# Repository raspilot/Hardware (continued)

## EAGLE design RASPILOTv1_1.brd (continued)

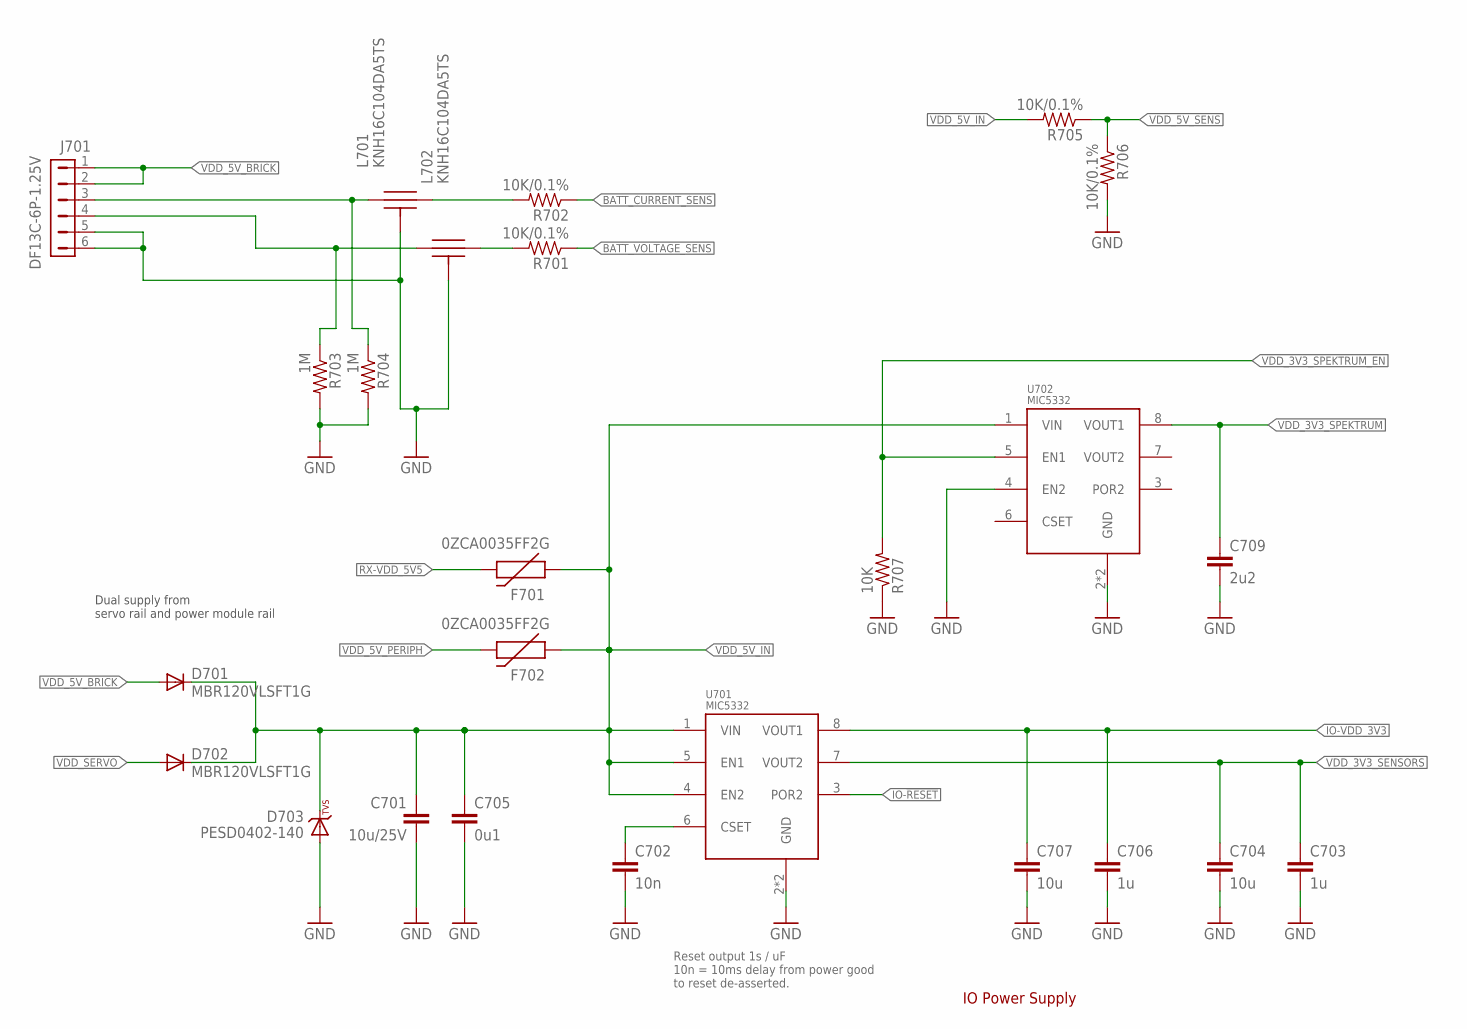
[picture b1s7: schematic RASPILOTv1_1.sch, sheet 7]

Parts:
C701: 10u/25V; 0805-CAP; PARTNO CL21A106KAYNNNE
C702: 10n; 0402-CAP; PARTNO CC0402KRX7R7BB103
C703, C706: 1u; 0603-CAP; PARTNO CC0603ZRY5V7BB105
C704, C707: 10u; 0603-CAP; PARTNO C1608X5R1A106K080AC
C705: 0u1; 0402-CAP; PARTNO CC0402ZRY5V7BB104
C709: 2u2; 0402-CAP; PARTNO C1005X6S1C225K050BC
D701, D702: MBR120VLSFT1G; SOD-123-DIO
D703: PESD0402-140; 0402-TVS; PARTNO PESD0402-140
F701, F702: 0ZCA0035FF2G; PTC-1206; PARTNO 0ZCA0035FF2G
J701: DF13C-6P-1.25V; PARTNO DF13C-6P-1.25V(20)
L701, L702: KNH16C104DA5TS; KYOCERA-KNH16-DA; PARTNO KNH16C104DA5TS
R701, R702, R705, R706: 10K/0.1%; 0402-RES; PARTNO ERA-2AEB103X
R703, R704: 1M; 0402-RES; PARTNO RC0402FR-071ML
R707: 10K; 0402-RES; PARTNO RC0402FR-0710KL
U701, U702: MIC5332; MLF-8-EPAD; PARTNO MIC5332-SSYMT

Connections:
BATT_CURRENT_SENS: R702.P$1 (1); also elsewhere on the board
BATT_CURRENT_SENS_PROT1: J701.3, L701.P$1, R704.P$1 (1)
BATT_VOLTAGE_SENS: R701.P$1 (1); also elsewhere on the board
BATT_VOLTAGE_SENS_PROT1: J701.4, L702.P$1, R703.P$1 (1)
GND: C701.P$2 (2), C702.P$2 (2), C703.P$2 (2), C704.P$2 (2), C705.P$2 (2), C706.P$2 (2), C707.P$2 (2), C709.P$2 (2), D703.A, J701.5, J701.6, L701.P$3, L701.P$4, L701.P$5, L702.P$3, L702.P$4, L702.P$5, R703.P$2 (2), R704.P$2 (2), R706.P$2 (2), R707.P$1 (1), U701.2 (GND), U701.GND, U702.2 (GND), U702.4 (EN2), U702.GND; also elsewhere on the board
IO-!RESET: U701.3 (POR2); also elsewhere on the board
IO-VDD_3V3: C706.P$1 (1), C707.P$1 (1), U701.8 (VOUT1); also elsewhere on the board
unnamed: L702.P$2, R701.P$2 (2)
unnamed: L701.P$2, R702.P$2 (2)
unnamed: C702.P$1 (1), U701.6 (CSET)
RX-VDD_5V5: F701.2; also elsewhere on the board
VDD_3V3_SENSORS: C703.P$1 (1), C704.P$1 (1), U701.7 (VOUT2); also elsewhere on the board
VDD_3V3_SPEKTRUM: C709.P$1 (1), U702.8 (VOUT1); also elsewhere on the board
VDD_3V3_SPEKTRUM_EN: R707.P$2 (2), U702.5 (EN1); also elsewhere on the board
VDD_5V_BRICK: D701.A, J701.1, J701.2; also elsewhere on the board
VDD_5V_IN: C701.P$1 (1), C705.P$1 (1), D701.C, D702.C, D703.C, F701.1, F702.1, R705.P$2 (2), U701.1 (VIN), U701.4 (EN2), U701.5 (EN1), U702.1 (VIN); also elsewhere on the board
VDD_5V_PERIPH: F702.2; also elsewhere on the board
VDD_5V_SENS: R705.P$1 (1), R706.P$1 (1); also elsewhere on the board
VDD_SERVO: D702.A; also elsewhere on the board

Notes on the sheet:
Dual supply from servo rail and power module rail
IO Power Supply
Reset output 1s / uF 10n = 10ms delay from power good to reset de-asserted.

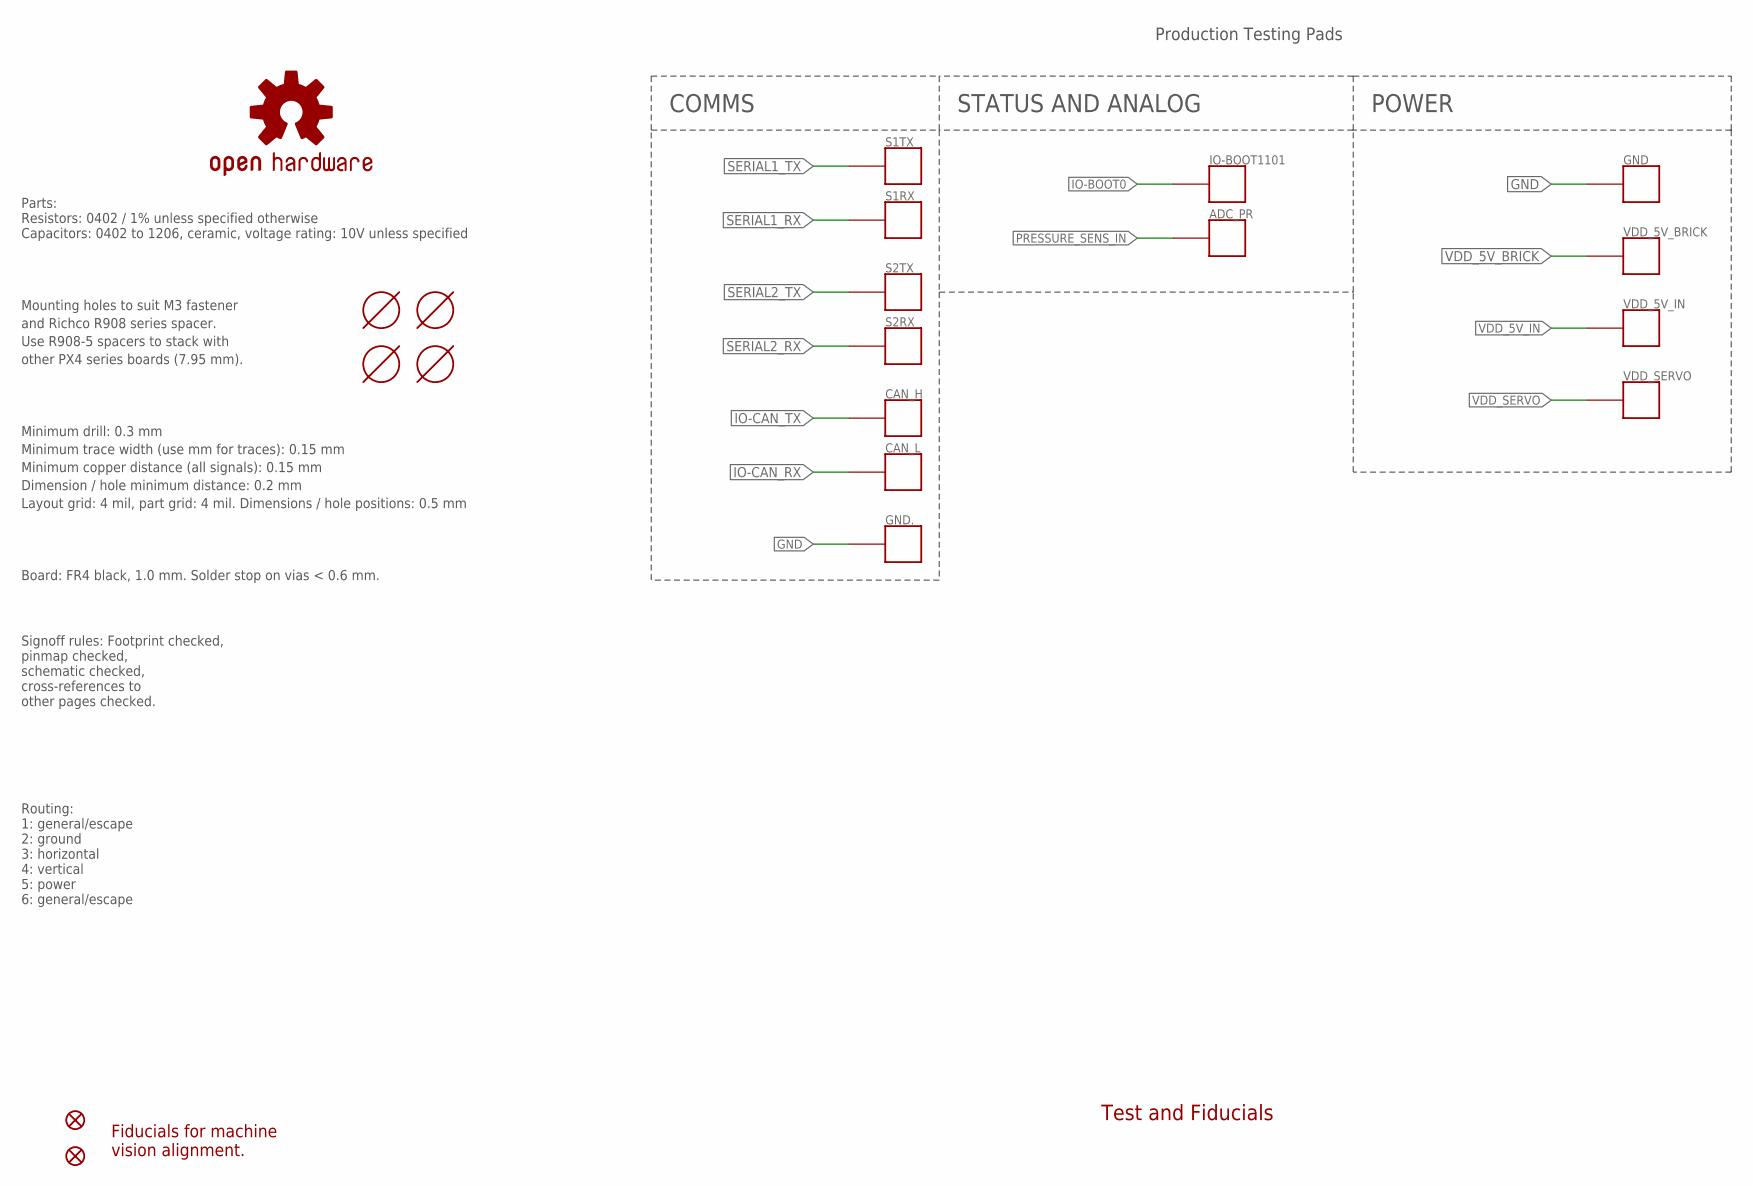
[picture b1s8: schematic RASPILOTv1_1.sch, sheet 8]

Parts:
ADC_PR: PAD.04; PAD.04X.04; PARTNO *
CAN_H: PAD.04; PAD.04X.04; PARTNO *
CAN_L: PAD.04; PAD.04X.04; PARTNO *
GND, GND.: PAD.04; PAD.04X.04; PARTNO *
IO-BOOT1101: PAD.04; PAD.04X.04; PARTNO *
JP1, JP2: FIDUCIAL1.5X3; FIDUCIAL-1.5X3; PARTNO *
M3_MOUNT1101, M3_MOUNT1102, M3_MOUNT1103, M3_MOUNT1104: MOUNT-HOLE3.1MM; MOUNT-HOLE3.1; PARTNO *
OSHW_LOGO: OSHW-LOGOS; OSHW-LOGO-S; PARTNO *
S1RX, S1TX, S2RX, S2TX: PAD.04; PAD.04X.04; PARTNO *
VDD_5V_BRICK, VDD_5V_IN: PAD.04; PAD.04X.04; PARTNO *
VDD_SERVO: PAD.04; PAD.04X.04; PARTNO *

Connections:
GND: GND.P$1, GND..P$1; also elsewhere on the board
IO-BOOT0: IO-BOOT1101.P$1; also elsewhere on the board
IO-CAN_RX: CAN_L.P$1; also elsewhere on the board
IO-CAN_TX: CAN_H.P$1; also elsewhere on the board
PRESSURE_SENS_IN: ADC_PR.P$1; also elsewhere on the board
SERIAL1_RX: S1RX.P$1; also elsewhere on the board
SERIAL1_TX: S1TX.P$1; also elsewhere on the board
SERIAL2_RX: S2RX.P$1; also elsewhere on the board
SERIAL2_TX: S2TX.P$1; also elsewhere on the board
VDD_5V_BRICK: VDD_5V_BRICK.P$1; also elsewhere on the board
VDD_5V_IN: VDD_5V_IN.P$1; also elsewhere on the board
VDD_SERVO: VDD_SERVO.P$1; also elsewhere on the board

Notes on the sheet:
Mounting holes to suit M3 fastener
and Richco R908 series spacer.
Use R908-5 spacers to stack with
other PX4 series boards (7.95 mm).
Production Testing Pads
Test and Fiducials
Minimum drill: 0.3 mm
Minimum trace width (use mm for traces): 0.15 mm
Minimum copper distance (all signals): 0.15 mm
Dimension / hole minimum distance: 0.2 mm
Layout grid: 4 mil, part grid: 4 mil. Dimensions / hole positions: 0.5 mm
Board: FR4 black, 1.0 mm. Solder stop on vias < 0.6 mm.
Signoff rules: Footprint checked, pinmap checked, schematic checked, cross-references to other pages checked.
Routing: 1: general/escape 2: ground 3: horizontal 4: vertical 5: power 6: general/escape
Fiducials for machine vision alignment.
Parts: Resistors: 0402 / 1% unless specified otherwise Capacitors: 0402 to 1206, ceramic, voltage rating: 10V unless specified
COMMS
POWER
STATUS AND ANALOG

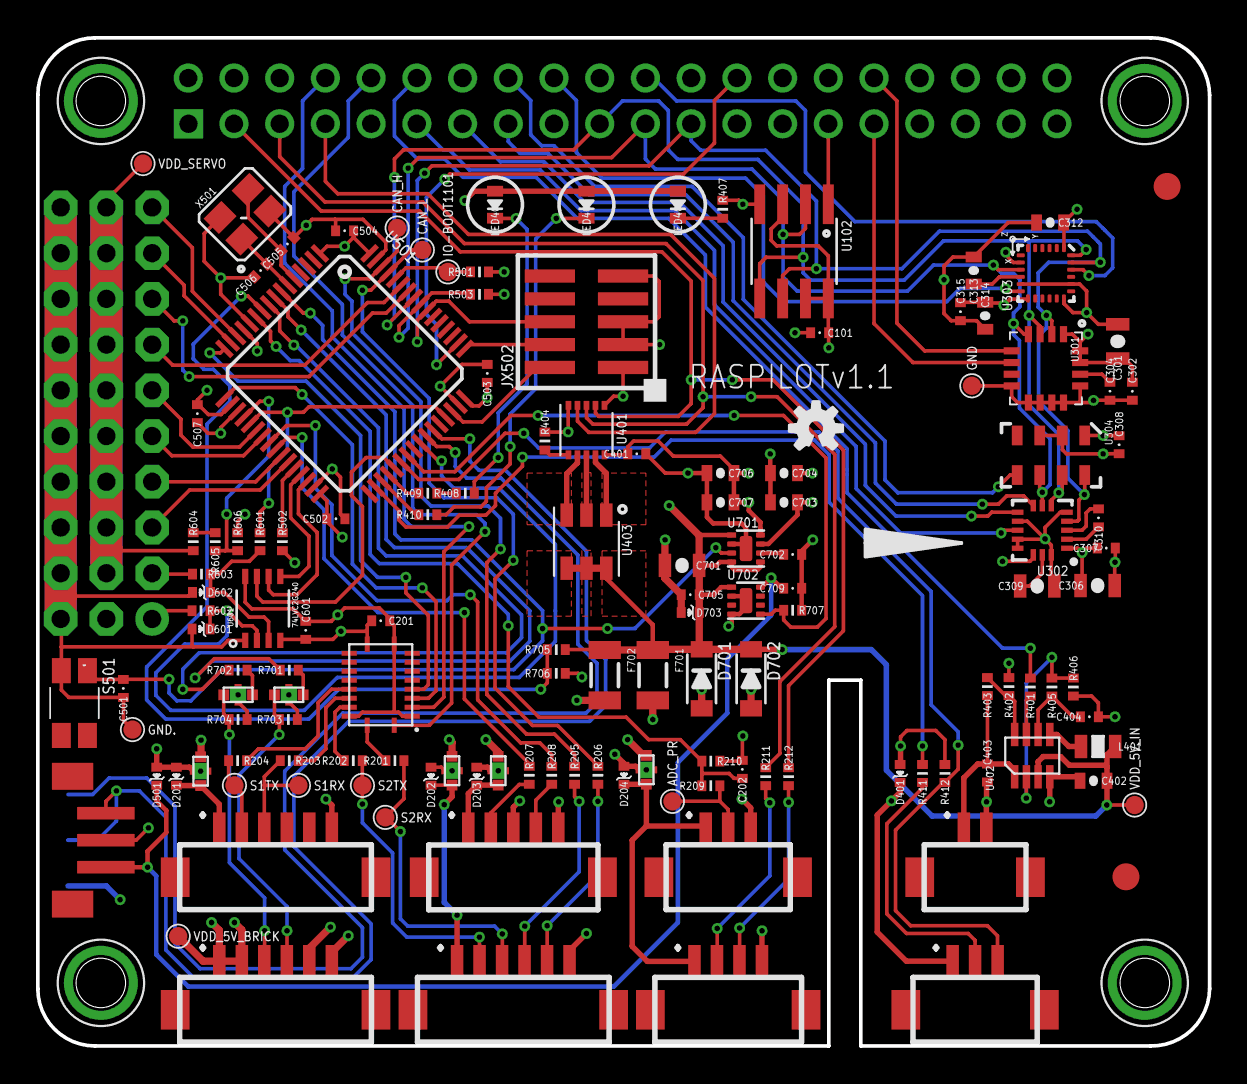
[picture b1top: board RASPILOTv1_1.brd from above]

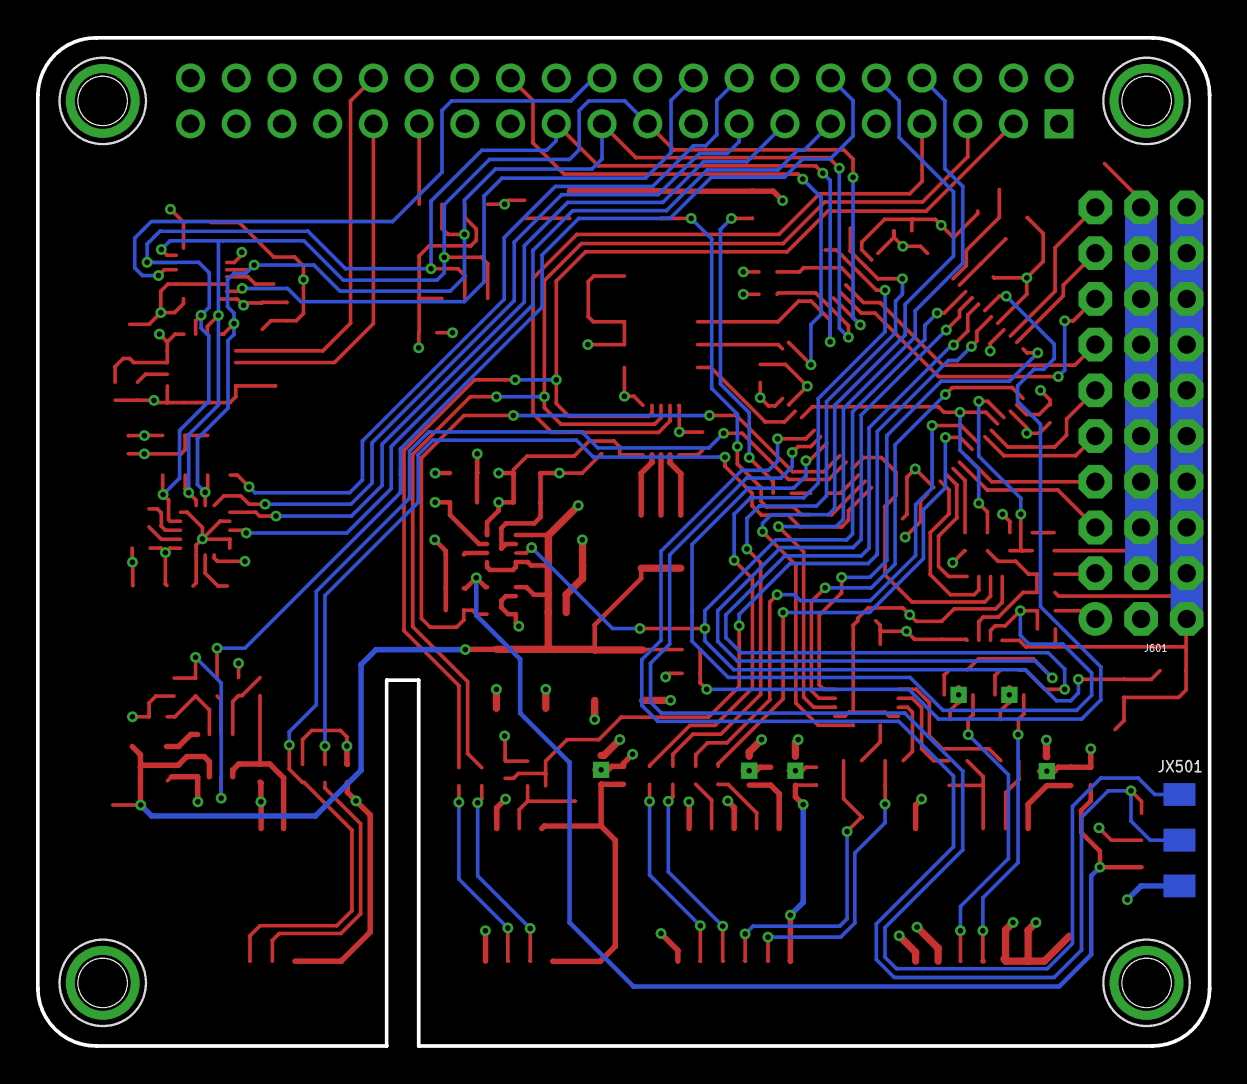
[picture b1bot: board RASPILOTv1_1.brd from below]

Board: 4 copper layers, 65.1 x 56.0 mm, 146 parts (2 on the bottom side), 114 nets.

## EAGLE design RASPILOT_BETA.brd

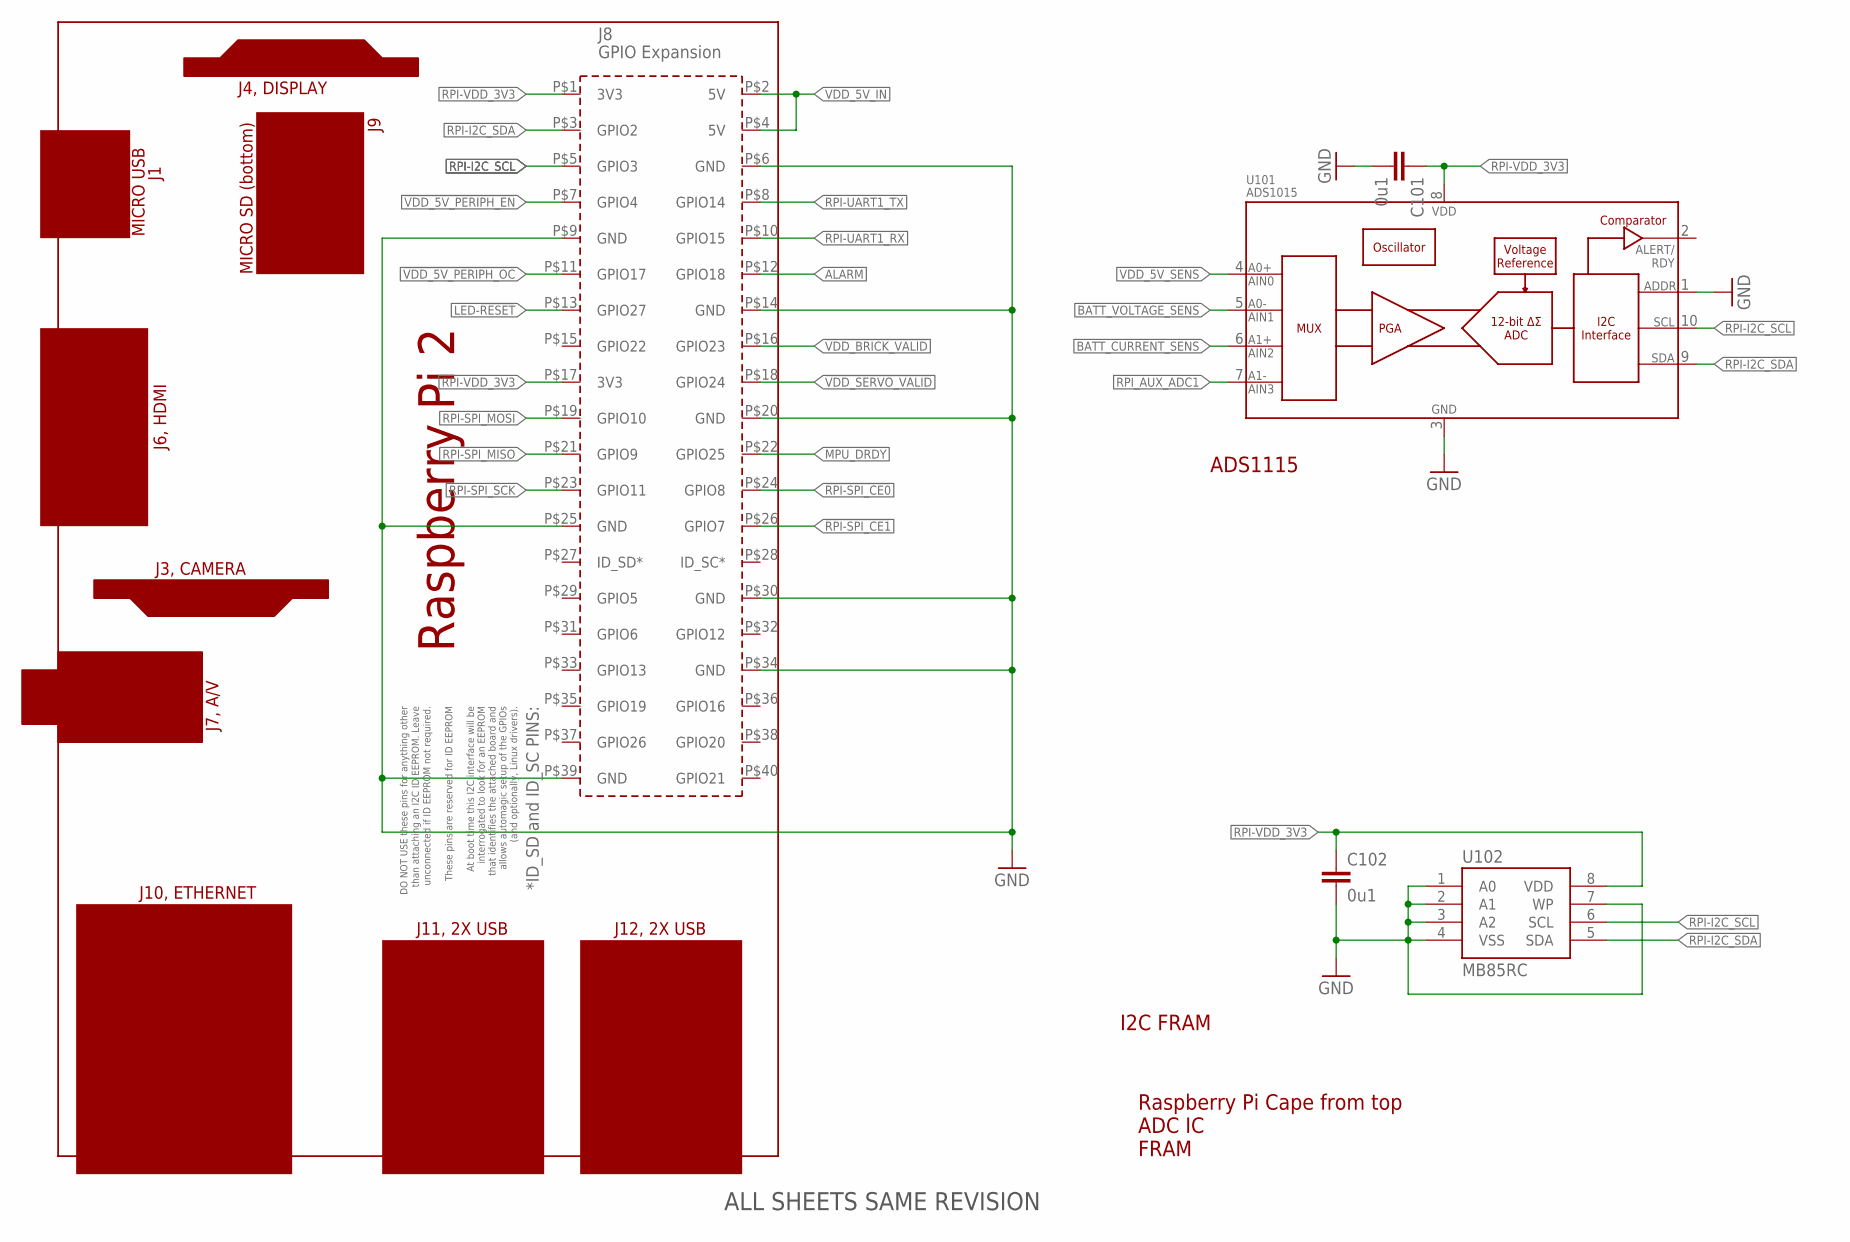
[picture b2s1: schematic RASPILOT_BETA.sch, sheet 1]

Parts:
C101, C102: 0u1; 0402-CAP; PARTNO CC0402ZRY5V7BB104
J101: RPI2
U101: ADS1015; MSOP10
U102: MB85RC; SOP8

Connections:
!RPI-SPI_CE0: J101.P$24 (GPIO8); also elsewhere on the board
!RPI-SPI_CE1: J101.P$26 (GPIO7); also elsewhere on the board
!VDD_5V_PERIPH_EN: J101.P$7 (GPIO4); also elsewhere on the board
!VDD_5V_PERIPH_OC: J101.P$11 (GPIO17); also elsewhere on the board
!VDD_BRICK_VALID: J101.P$16 (GPIO23); also elsewhere on the board
!VDD_SERVO_VALID: J101.P$18 (GPIO24); also elsewhere on the board
ALARM: J101.P$12 (GPIO18); also elsewhere on the board
BATT_CURRENT_SENS: U101.6 (AIN2); also elsewhere on the board
BATT_VOLTAGE_SENS: U101.5 (AIN1); also elsewhere on the board
GND: C101.P$2 (2), C102.P$2 (2), J101.P$6 (GND), J101.P$9 (GND), J101.P$14 (GND), J101.P$20 (GND), J101.P$25 (GND), J101.P$30 (GND), J101.P$34 (GND), J101.P$39 (GND), U101.1 (ADDR), U101.3 (VSS), U102.1 (A0), U102.2 (A1), U102.3 (A2), U102.4 (VSS), U102.7 (WP); also elsewhere on the board
LED-!RESET: J101.P$13 (GPIO27); also elsewhere on the board
MPU_DRDY: J101.P$22 (GPIO25); also elsewhere on the board
RPI-I2C_SCL: J101.P$5 (GPIO3), U101.10 (SCL), U102.6 (SCL); also elsewhere on the board
RPI-I2C_SDA: J101.P$3 (GPIO2), U101.9 (SDA), U102.5 (SDA); also elsewhere on the board
RPI-SPI_MISO: J101.P$21 (GPIO9); also elsewhere on the board
RPI-SPI_MOSI: J101.P$19 (GPIO10); also elsewhere on the board
RPI-SPI_SCK: J101.P$23 (GPIO11); also elsewhere on the board
RPI-UART1_RX: J101.P$10 (GPIO15); also elsewhere on the board
RPI-UART1_TX: J101.P$8 (GPIO14); also elsewhere on the board
RPI-VDD_3V3: C101.P$1 (1), C102.P$1 (1), J101.P$1 (3V3), J101.P$17 (3V3), U101.8 (VDD), U102.8 (VDD); also elsewhere on the board
RPI_AUX_ADC1: U101.7 (AIN3); also elsewhere on the board
VDD_5V_IN: J101.P$2 (5V), J101.P$4 (5V); also elsewhere on the board
VDD_5V_SENS: U101.4 (AIN0); also elsewhere on the board

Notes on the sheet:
Raspberry Pi Cape from top ADC IC FRAM
ALL SHEETS SAME REVISION
ADS1115
I2C FRAM

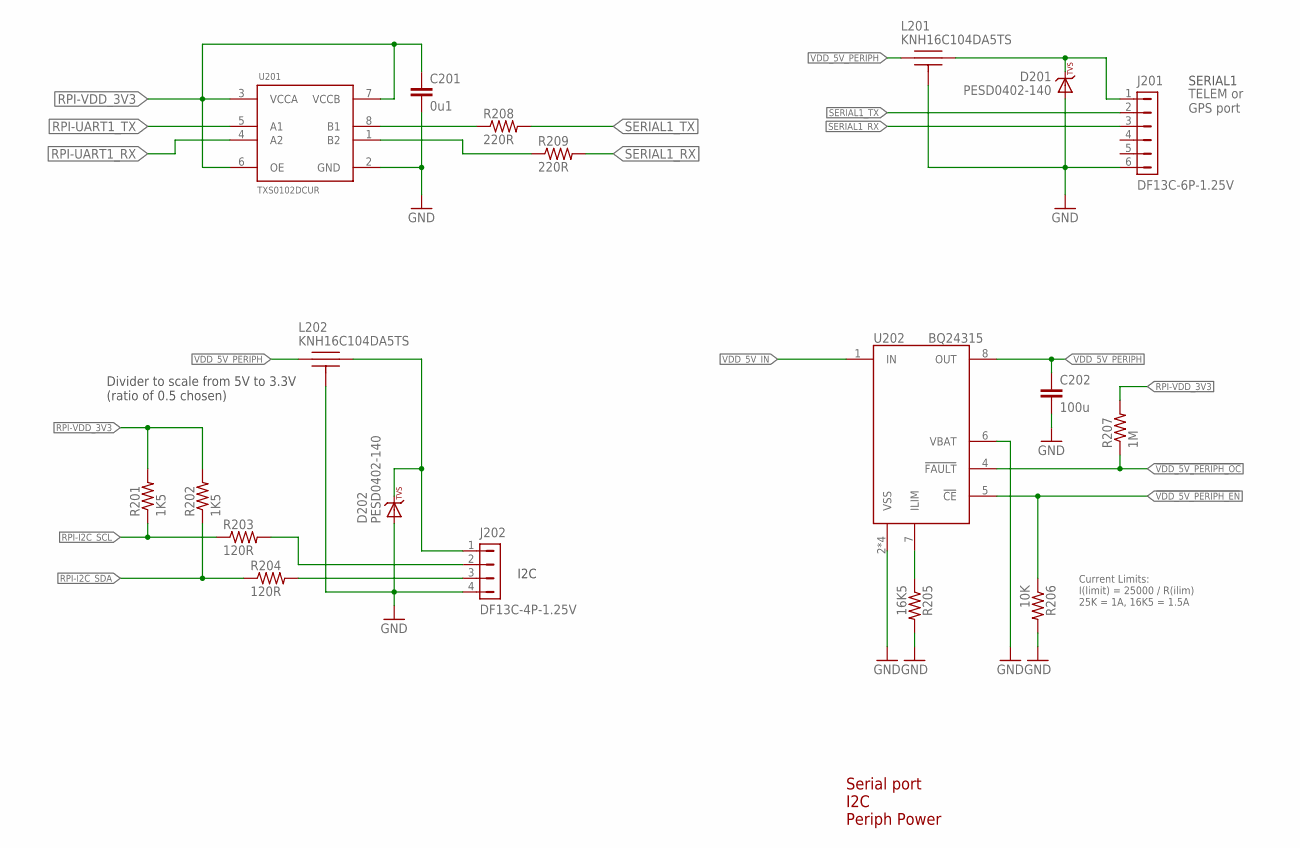
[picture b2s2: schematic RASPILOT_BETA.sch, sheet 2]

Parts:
C201: 0u1; 0402-CAP; PARTNO CC0402ZRY5V7BB104
C202: 100u; 1206-CAP; PARTNO C3216X5R1A107M160AC
D201, D202: PESD0402-140; 0402-TVS; PARTNO PESD0402-140
J201: DF13C-6P-1.25V; PARTNO DF13C-6P-1.25V(20)
J202: DF13C-4P-1.25V; PARTNO DF13C-4P-1.25V(20)
L201, L202: KNH16C104DA5TS; KYOCERA-KNH16-DA; PARTNO KNH16C104DA5TS
R201, R202: 1K5; 0402-RES; PARTNO RC0402FR-071K5L
R203, R204: 120R; 0402-RES; PARTNO RC0402FR-07120RL
R205: 16K5; 0402-RES; PARTNO RMCF0402FT25K5
R206: 10K; 0402-RES; PARTNO RC0402FR-0710KL
R207: 1M; 0402-RES; PARTNO RC0402FR-071ML
R208, R209: 220R; 0402-RES; PARTNO RC0402FR-07220RL
U201: TXS0102DCUR; TI-DCU
U202: BQ24315; QFN8-DSG; PARTNO BQ24315DSGR

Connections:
!VDD_5V_PERIPH_EN: R206.P$1 (1), U202.5 (!CE); also elsewhere on the board
!VDD_5V_PERIPH_OC: R207.P$1 (1), U202.4 (!FAULT); also elsewhere on the board
GND: C201.P$2 (2), C202.P$2 (2), D201.A, D202.A, J201.6, J202.4, L201.P$3, L201.P$4, L201.P$5, L202.P$3, L202.P$4, L202.P$5, R205.P$2 (2), R206.P$2 (2), U201.2 (GND), U202.2 (VSS), U202.6 (VBAT), U202.GND (VSS), U202.P$2 (VSS), U202.P$3 (VSS); also elsewhere on the board
unnamed: J202.2, R203.P$2 (2)
unnamed: J202.3, R204.P$2 (2)
unnamed: D202.C, J202.1, L202.P$2
unnamed: R208.P$1 (1), U201.8 (B1)
unnamed: R209.P$1 (1), U201.1 (B2)
unnamed: R205.P$1 (1), U202.7 (ILIM)
unnamed: D201.C, J201.1, L201.P$2
RPI-I2C_SCL: R201.P$1 (1), R203.P$1 (1); also elsewhere on the board
RPI-I2C_SDA: R202.P$1 (1), R204.P$1 (1); also elsewhere on the board
RPI-UART1_RX: U201.4 (A2); also elsewhere on the board
RPI-UART1_TX: U201.5 (A1); also elsewhere on the board
RPI-VDD_3V3: C201.P$1 (1), R201.P$2 (2), R202.P$2 (2), R207.P$2 (2), U201.3 (VCCA), U201.6 (OE), U201.7 (VCCB); also elsewhere on the board
SERIAL1_RX: J201.3, R209.P$2 (2); also elsewhere on the board
SERIAL1_TX: J201.2, R208.P$2 (2); also elsewhere on the board
VDD_5V_IN: U202.1 (IN); also elsewhere on the board
VDD_5V_PERIPH: C202.P$1 (1), L201.P$1, L202.P$1, U202.8 (OUT)

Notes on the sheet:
Serial port I2C Periph Power
SERIAL1
TELEM or GPS port
I2C
Divider to scale from 5V to 3.3V (ratio of 0.5 chosen)
Current Limits: I(limit) = 25000 / R(ilim) 25K = 1A, 16K5 = 1.5A

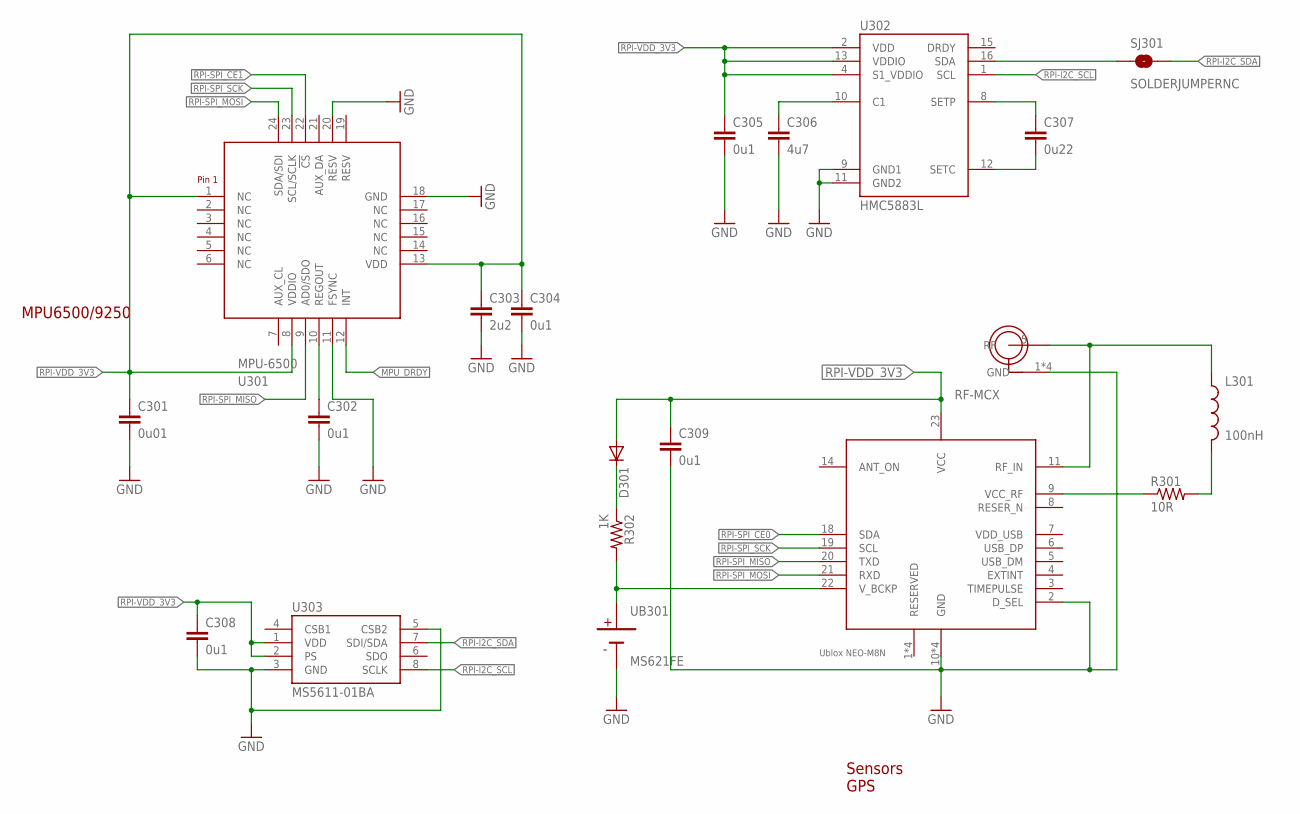
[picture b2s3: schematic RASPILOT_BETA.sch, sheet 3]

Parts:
C301: 0u01; 0402-CAP; PARTNO CC0402ZRY5V7BB104
C302, C304, C305, C308, C309: 0u1; 0402-CAP; PARTNO CC0402ZRY5V7BB104
C303: 2u2; 0603-CAP; PARTNO C1608X6S1C225K080AC
C306: 4u7; 0603-CAP; PARTNO C1608X6S1C225K080AC
C307: 0u22; 0402-CAP; PARTNO CC0402ZRY5V7BB104
D301: DIODE-0603; 0603-DIO
J301: RF-MCX; RF-MCX-H
L301: 100nH; 0603-IND
R301: 10R; 0603-RES
R302: 1K; 0402-RES; PARTNO RMCF0402FT16K5
SJ301: SOLDERJUMPERNC; SJ_2S
U301: MPU-6500
U302: HMC5883L; HMC5883L-MAN
U303: MS5611-01BA; PARTNO MS5611-01BA
U304: NEO-M8N
UB301: MS621FE

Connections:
!RPI-SPI_CE0: U304.18 (SDA); also elsewhere on the board
!RPI-SPI_CE1: U301.22 (!CS); also elsewhere on the board
GND: C301.P$2 (2), C302.P$2 (2), C303.P$2 (2), C304.P$2 (2), C305.P$2 (2), C306.P$2 (2), C308.P$2 (2), C309.P$2 (2), J301.1 (GND), J301.2 (GND), J301.3 (GND), J301.4 (GND), U301.11 (FSYNC), U301.18 (GND), U301.20 (RESV), U302.9 (GND1), U302.11 (GND2), U303.3 (GND), U303.5 (CSB2), U304.2 (D_SEL), U304.10 (GND), U304.12 (GND), U304.13 (GND), U304.24 (GND), UB301.2 (NEG); also elsewhere on the board
MPU_DRDY: U301.12 (INT); also elsewhere on the board
unnamed: C302.P$1 (1), U301.10 (REGOUT)
unnamed: C306.P$1 (1), U302.10 (C1)
unnamed: C307.P$1 (1), U302.8 (SETP)
unnamed: C307.P$2 (2), U302.12 (SETC)
unnamed: SJ301.1, U302.16 (SDA)
unnamed: J301.5 (RF), L301.P$1 (1), U304.11 (RF_IN)
unnamed: R302.P$2 (2), U304.22 (V_BCKP), UB301.1 (POS)
unnamed: R301.1, U304.9 (VCC_RF)
unnamed: L301.P$2 (2), R301.2
unnamed: D301.C, R302.P$1 (1)
RPI-I2C_SCL: U302.1 (SCL), U303.8 (SCLK); also elsewhere on the board
RPI-I2C_SDA: SJ301.2, U303.7 (SDI/SDA); also elsewhere on the board
RPI-SPI_MISO: U301.9 (AD0/SDO), U304.20 (TXD); also elsewhere on the board
RPI-SPI_MOSI: U301.24 (SDA/SDI), U304.21 (RXD); also elsewhere on the board
RPI-SPI_SCK: U301.23 (SCL/SCLK), U304.19 (SCL); also elsewhere on the board
RPI-VDD_3V3: C301.P$1 (1), C303.P$1 (1), C304.P$1 (1), C305.P$1 (1), C308.P$1 (1), C309.P$1 (1), D301.A, U301.1 (NC), U301.8 (VDDIO), U301.13 (VDD), U302.2 (VDD), U302.4 (S1_VDDIO), U302.13 (VDDIO), U303.1 (VDD), U303.2 (PS), U304.23 (VCC); also elsewhere on the board

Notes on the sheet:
Sensors GPS
MPU6500/9250

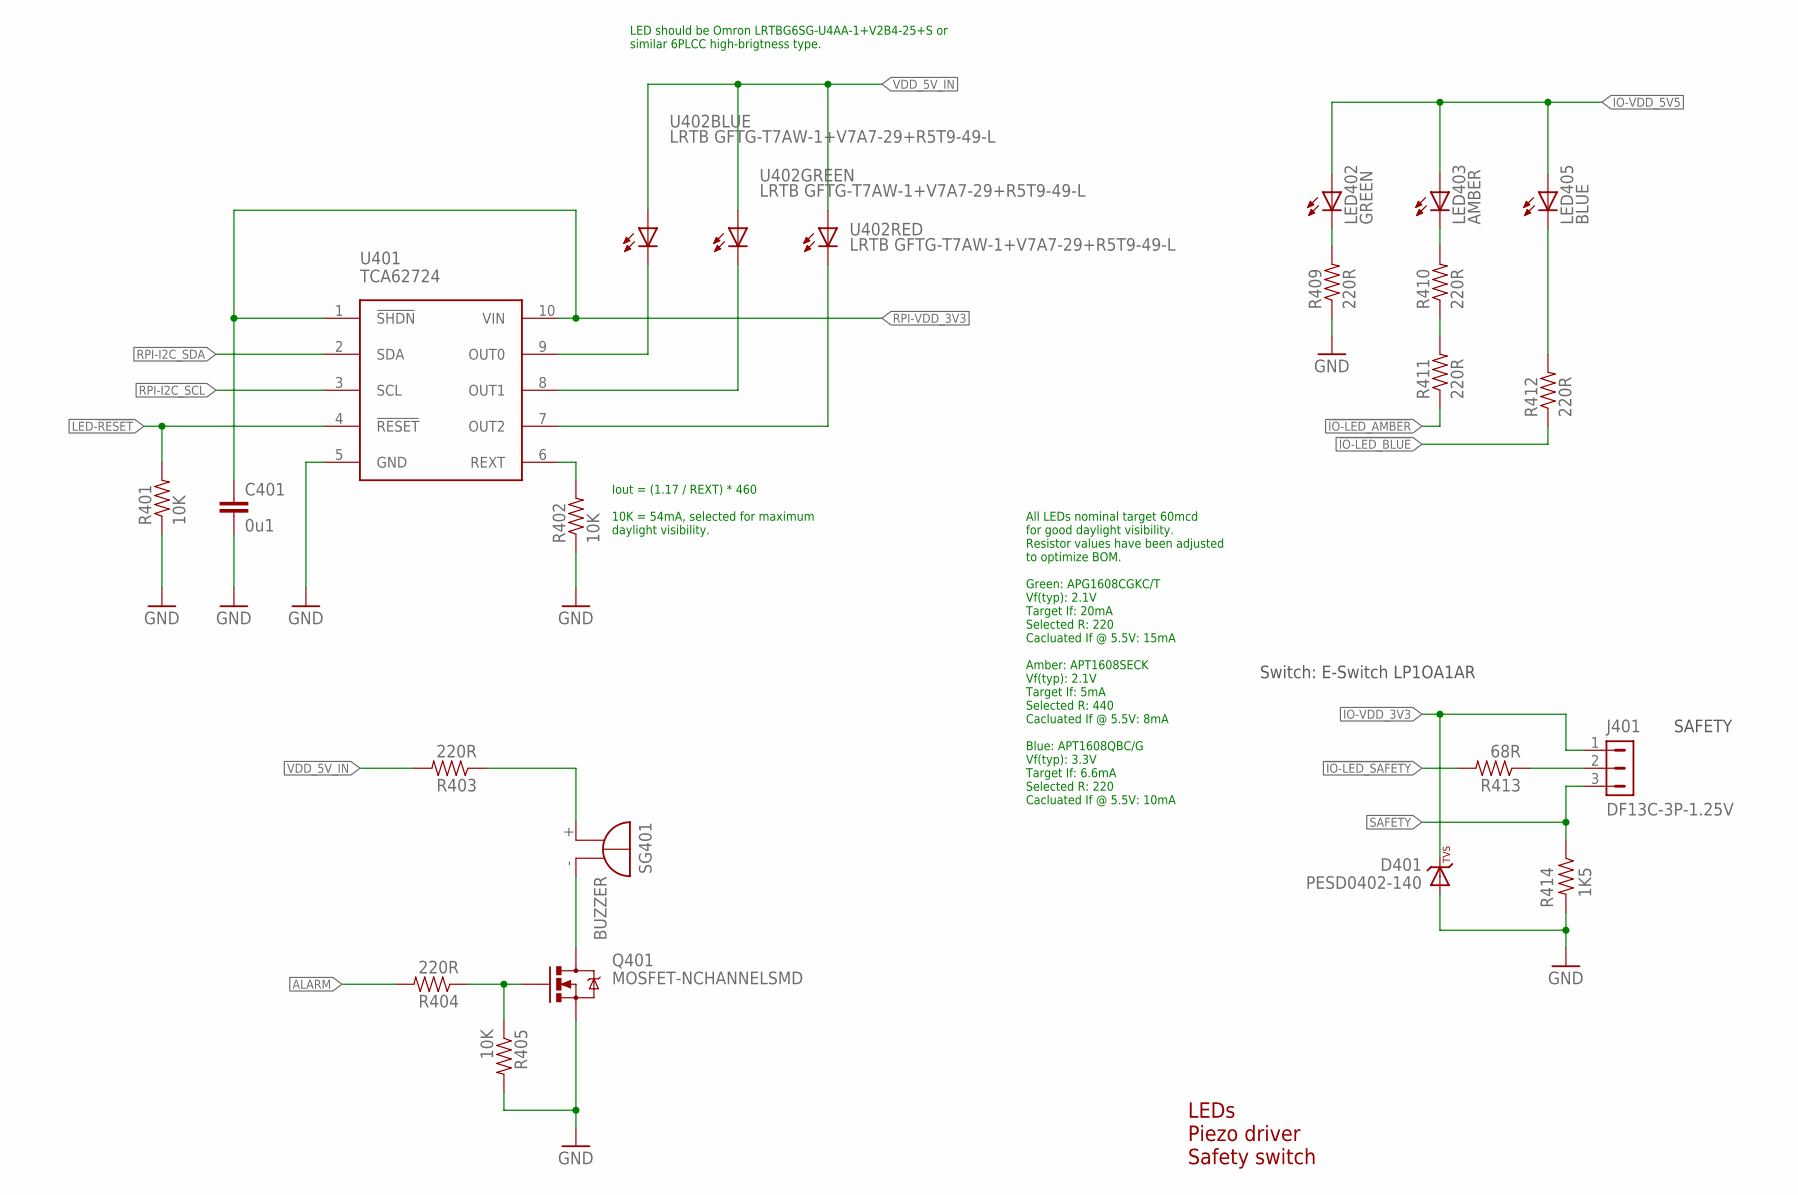
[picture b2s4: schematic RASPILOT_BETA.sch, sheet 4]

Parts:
C401: 0u1; 0402-CAP; PARTNO CC0402ZRY5V7BB104
D401: PESD0402-140; 0402-TVS; PARTNO PESD0402-140
J401: DF13C-3P-1.25V; PARTNO DF13C-3P-1.25V(20)
LED402: GREEN; 0603-LED; PARTNO APTD1608CGCK
LED403: AMBER; 0603-LED; PARTNO APTD1608SECK
LED405: BLUE; 0603-LED; PARTNO APTD1608QBC/D
Q401: MOSFET-NCHANNELSMD; SOT23-3
R401, R402: 10K; 0402-RES; PARTNO RC0402FR-0710KL
R403: 220R; 0402-RES; PARTNO RMCF0402FT16K5
R404: 220R; 0402-RES; PARTNO RMCF0402FT9K09
R405: 10K; 0402-RES; PARTNO RMCF0402FT9K09
R409, R410, R411, R412: 220R; 0402-RES; PARTNO RC0402FR-07220RL
R413: 68R; 0402-RES; PARTNO ERJ-2GEJ680X
R414: 1K5; 0402-RES; PARTNO RC0402FR-071K5L
SG401: BUZZER; F/TMB
U401: TCA62724FMG; SON10; PARTNO TCA62724FMG
U402: LRTB GFTG-T7AW-1+V7A7-29+R5T9-49-L; 6-PLCC; PARTNO LRTB GFTG-T7AW-1+V7A7-29+R5T9-49-L

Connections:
!IO-LED_AMBER: R411.P$1 (1); also elsewhere on the board
!IO-LED_BLUE: R412.P$1 (1); also elsewhere on the board
!IO-LED_SAFETY: R413.P$2 (2); also elsewhere on the board
ALARM: R404.P$2 (2); also elsewhere on the board
GND: C401.P$2 (2), D401.A, Q401.2 (S), R401.P$1 (1), R402.P$1 (1), R405.P$2 (2), R409.P$1 (1), R414.P$2 (2), U401.5 (GND); also elsewhere on the board
IO-VDD_3V3: D401.C, J401.1; also elsewhere on the board
IO-VDD_5V5: LED402.A, LED403.A, LED405.A; also elsewhere on the board
LED-!RESET: R401.P$2 (2), U401.4 (!RESET); also elsewhere on the board
unnamed: Q401.1 (G), R404.P$1 (1), R405.P$1 (1)
unnamed: LED405.C, R412.P$2 (2)
unnamed: R403.P$1 (1), SG401.+
unnamed: Q401.3 (D), SG401.-
unnamed: LED402.C, R409.P$2 (2)
unnamed: R410.P$1 (1), R411.P$2 (2)
unnamed: LED403.C, R410.P$2 (2)
unnamed: J401.2, R413.P$1 (1)
unnamed: R402.P$2 (2), U401.6 (REXT)
RGB_LED_3: U401.9 (OUT0), U402.C1 (C)
RGB_LED_4: U401.8 (OUT1), U402.C2 (C)
RGB_LED_14: U401.7 (OUT2), U402.C3 (C)
RPI-I2C_SCL: U401.3 (SCL); also elsewhere on the board
RPI-I2C_SDA: U401.2 (SDA); also elsewhere on the board
RPI-VDD_3V3: C401.P$1 (1), U401.1 (!SHDN), U401.10 (VIN); also elsewhere on the board
SAFETY: J401.3, R414.P$1 (1); also elsewhere on the board
VDD_5V_IN: R403.P$2 (2), U402.A1 (A), U402.A2 (A), U402.A3 (A); also elsewhere on the board

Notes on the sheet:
LEDs Piezo driver Safety switch
Switch: E-Switch LP1OA1AR
SAFETY
LED should be Omron LRTBG6SG-U4AA-1+V2B4-25+S or similar 6PLCC high-brigtness type.
Iout = (1.17 / REXT) * 460 10K = 54mA, selected for maximum daylight visibility.
All LEDs nominal target 60mcd for good daylight visibility. Resistor values have been adjusted to optimize BOM. Green: APG1608CGKC/T Vf(typ): 2.1V Target If: 20mA Selected R: 220 Cacluated If @ 5.5V: 15mA Amber: APT1608SECK Vf(typ): 2.1V Target If: 5mA Selected R: 440 Cacluated If @ 5.5V: 8mA Blue: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
